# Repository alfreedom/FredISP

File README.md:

# FredISP 

### AVR USB ISP programmer based on the FabISP project.

The FredISP is a tiny, low cost and opern source usb ISP programmer for AVR microcontrollers.

This project is based on the FabISP programmer and the V-USB usign USBtiny firmware and drivers.

The programmer is compatible with Windows, MacOS and Linux.

##### Project structure:

* Firmware folder: contains the firmware for the FredISP board. It was created with APOS tool and compiled for the ATtiny4 microcontroller running at 16 Mhz.
* Hardware folder: Contains the schematic and board Eagle files for the FredISP programmer.

----

### Installation

The programmer works with the usbtiny software, so the PC will recognize it as such. Linux and MacOS do not need to install drivers, the avrdude fotware is compatible with this programmer.

In Windows it is necessary to install the USBTiny driver of Adafruit® and the avrdude program. The driver installer is in the "drivers" folder. After having installed it, it will appear as "USBtiny" in the device manager.

To use the programmer it is necessary to install the avrdude software, which is available for Linux, MacOS and Windows systems.

In Linux operating systems it can be installed with the following commands:

Debian and derivates:

```bash
    sudo apt-get install avrdude
```

Fedora and RedHat:

```bash
    sudo yum install avrdude
```

Achr Linux and Derivates:

```bash
    sudo pacman -Sy avrdude
```

On MacOS operating systems it is possible to install it using homebrew:

```bash
    brew install avrdude
```

For Windows it is necessary to download the avrdude program executables and install them, preferably in the path C: \ windows \ avrdude. You must also add the installation folder to the end of the system path variablae.

[Download avrdude for windows](http://download.savannah.gnu.org/releases/avrdude/avrdude-6.3-mingw32.zip "avrdude download for Windows")

To use the FredISP with avrdude, you only need to specify the "usbtiny" programmer in the -c command line option, eg:

 avrdude __-c usbtiny__ -p atmega328p

---
### Linux users

In Linux it is necessary to make some configurations so that the avrdude program and the programmer are used without administrator's permission.

First you have to add your user to the "dialout" group (in debian based distributions) with the command:

``` bash
sudo adduser MYUSER dialout
``` 

Then you have to create the file with the device rules for avrdude in the path /etc/udev/rules.d (the path of the udev folder may vary from one system to another). It can be created with the following command:

``` bash
sudo touch /etc/udev/rules.d/99-avr.rules
``` 

You have to add the definitions of the programmers by editing the file:

``` bash
sudo nano /etc/udev/rules.d/99-avr.rules
``` 

``` bash
# Programmers for avrdude
ATTR{idVendor}=="03eb", ATTR{idProduct}=="2104", GROUP="dialout", MODE="0660" # AVRISP mkII
ATTR{idVendor}=="03eb", ATTR{idProduct}=="2107", GROUP="dialout", MODE="0660" # AVR-Dragon
ATTR{idVendor}=="03eb", ATTR{idProduct}=="2103", GROUP="dialout", MODE="0660" # JTAG ICE mkII
ATTR{idVendor}=="03eb", ATTR{idProduct}=="2106", GROUP="dialout", MODE="0660" # STK600
ATTR{idVendor}=="16c0", ATTR{idProduct}=="05dc", GROUP="dialout", MODE="0660" # USBASP von www.fischl.de
ATTR{idVendor}=="03eb", ATTR{idProduct}=="2ffa", GROUP="dialout", MODE="0660" # AT90USB
ATTR{idVendor}=="10c4", ATTR{idProduct}=="ea60", GROUP="dialout", MODE="0660" # AVR910
ATTR{idVendor}=="03eb", ATTR{idProduct}=="2105", GROUP="dialout", MODE="0660" # AVR ONE
ATTR{idVendor}=="03eb", ATTR{idProduct}=="210d", GROUP="dialout", MODE="0660" # Atmel XPLAIN CDC Gateway
ATTR{idVendor}=="03eb", ATTR{idProduct}=="2ffb", GROUP="dialout", MODE="0660" # AT90USB AVR DFU bootloader
ATTR{idVendor}=="1781", ATTR{idProduct}=="0c9f", GROUP="dialout", MODE="0660" # usbtiny
```
The group of udev rules depend of the Linux distribution, you need to check which group have the permissions to control the hardware, for example in Manjaro and Arch linux the group is __uucp__. 

And finally reload the device rules for the changes to take effect:

```bash
sudo udevadm control --reload 
sudo udevadm trigger --action=add
```

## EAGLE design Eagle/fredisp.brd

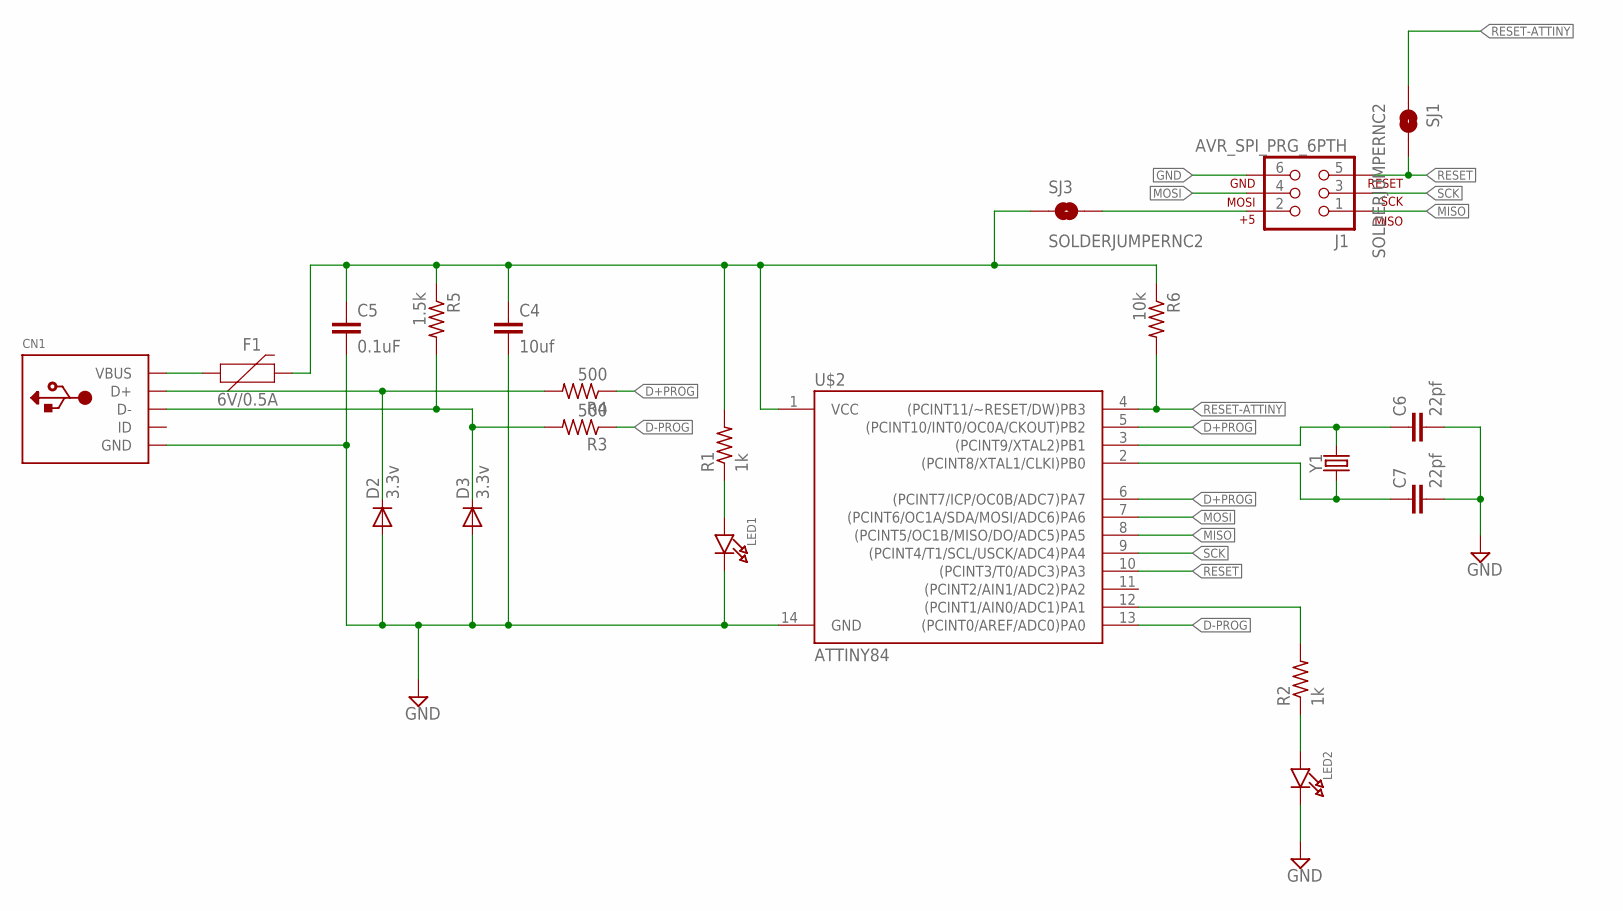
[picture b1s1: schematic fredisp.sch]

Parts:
C4: 10uf; C1206
C5: 0.1uF; C0805
C6, C7: 22pf; C0805
CN1: USBMINIB; USB-MINIB
D2, D3: 3.3v; SOD323-W
F1: 6V/0.5A; 1206
J1: AVR_SPI_PRG_6PTH; 2X3
LED1, LED2: LED0805; CHIPLED_0805
R1, R2: 1k; R0805
R3, R4: 500; R0805
R5: 1.5k; R0805
R6: 10k; R0805
SJ1, SJ3: SOLDERJUMPERNC2; SJ_2S-NOTRACE
U$2: ATTINY84; SO14
Y1: CRYSTALSMD-3.2X2.5; CRYSTAL-SMD-3.2X2.5MM

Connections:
D+PROG: R4.1, U$2.5 ((PCINT10/INT0/OC0A/CKOUT)PB2), U$2.6 ((PCINT7/ICP/OC0B/ADC7)PA7)
D-PROG: R3.1, U$2.13 ((PCINT0/AREF/ADC0)PA0)
GND: C4.2, C5.2, C6.2, C7.2, CN1.GND, D2.A, D3.A, J1.6, LED1.C, LED2.C, U$2.14 (GND)
MISO: J1.1, U$2.8 ((PCINT5/OC1B/MISO/DO/ADC5)PA5)
MOSI: J1.4, U$2.7 ((PCINT6/OC1A/SDA/MOSI/ADC6)PA6)
unnamed: C6.1, U$2.3 ((PCINT9/XTAL2)PB1), Y1.3 (2)
unnamed: CN1.D-, D3.C, R3.2, R5.2
unnamed: CN1.D+, D2.C, R4.2
unnamed: C7.1, U$2.2 ((PCINT8/XTAL1/CLKI)PB0), Y1.1
unnamed: J1.2, SJ3.2
unnamed: CN1.VBUS, F1.1
unnamed: LED1.A, R1.1
unnamed: LED2.A, R2.1
unnamed: R2.2, U$2.12 ((PCINT1/AIN0/ADC1)PA1)
RESET: J1.5, SJ1.2, U$2.10 ((PCINT3/T0/ADC3)PA3)
RESET-ATTINY: R6.2, SJ1.1, U$2.4 ((PCINT11/~RESET/DW)PB3)
SCK: J1.3, U$2.9 ((PCINT4/T1/SCL/USCK/ADC4)PA4)
VCC: C4.1, C5.1, F1.2, R1.2, R5.1, R6.1, SJ3.1, U$2.1 (VCC)

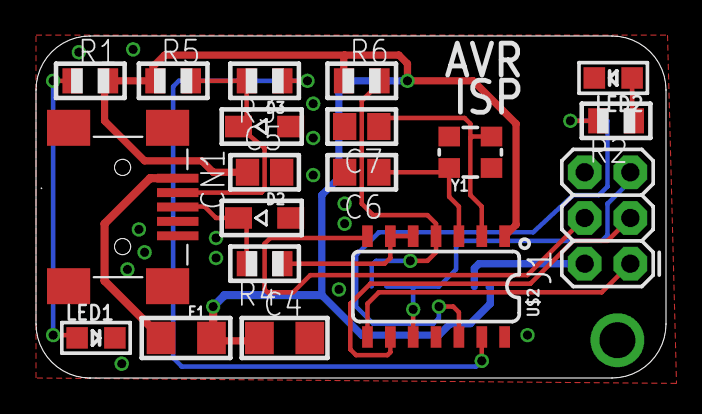
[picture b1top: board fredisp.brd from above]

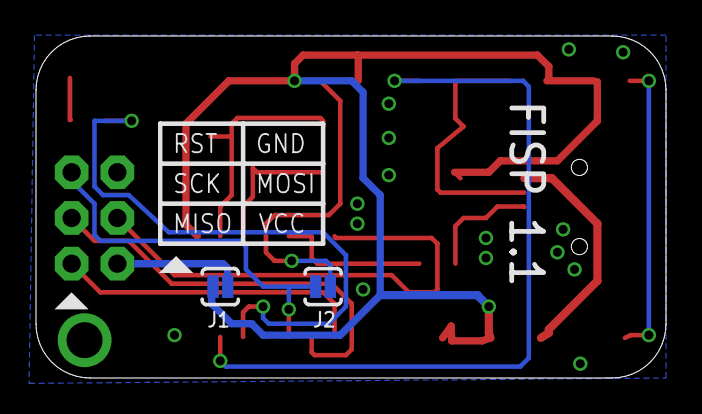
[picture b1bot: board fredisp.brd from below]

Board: 2 copper layers, 35.0 x 19.0 mm, 21 parts (2 on the bottom side), 18 nets.

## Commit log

2018-04-07 Add FredISP v1.0
2018-09-03 FredISP v1.1
    - Update the SMD Zener diode footprint
    - Update Panelized Gerbers with frame
    - Add 3D model in STEP and Freecad format.

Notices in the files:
parts and their libraries:
microbuilder: This work is placed in the public domain, and may be freely used for commercial and non-commercial work with the following conditions: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
SparkFun-Connectors: Licensing: Creative Commons ShareAlike 4.0 International - https://creativecommons.org/licenses/by-sa/4.0
